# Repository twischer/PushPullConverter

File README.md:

PushPullConverter
=================

Half-bridge push-pull converter to convert 12 volt to higher voltage

There are assembled circuits available which reduces the complexity of this circuit and
might improve the efficiency.
Search for "EG7500 Inverter switching power driver board compatible KA7500 TL494" to find them.

Status
------
I am able to light up a 60W light bulb without rectifier secondary site in use.
But when using the rectifier the efficiency drops to ~50%.

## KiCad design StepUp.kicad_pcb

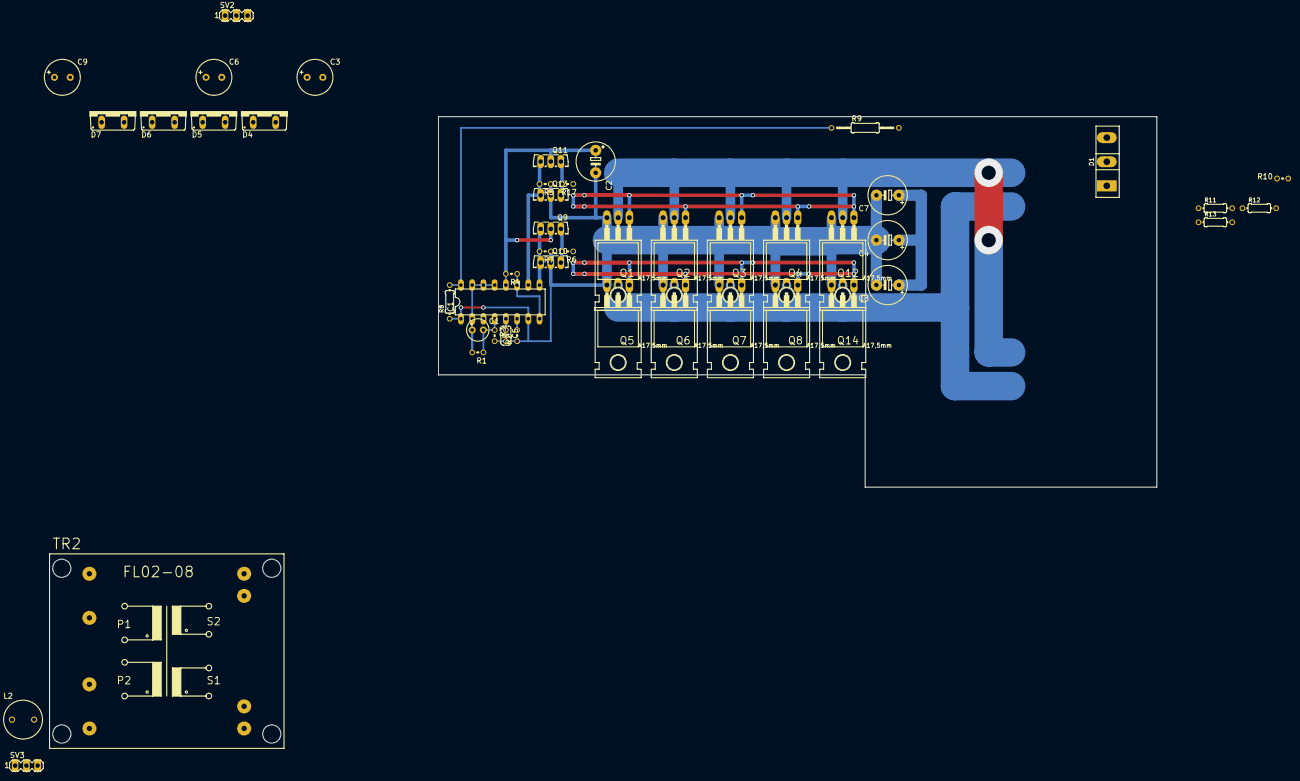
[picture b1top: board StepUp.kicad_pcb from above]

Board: 2 copper layers, 162.5 x 83.8 mm, 47 parts (0 on the bottom side), 27 nets.

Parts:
C1: 10µ; E2,5-5
C2: 1000µ; E5-8,5
C3, C6, C9: CPOL-EUE3.5-8; E3,5-8
C4, C7, C8: 3300µ; E5-8,5
C5: 1n; C025-024X044
D1: MBR20200CT; TO-247-3_Vertical
D4, D5, D6, D7: BYT08P; TO220ACS
IC1: TL494N; DIL16
L2: 10µ; 6000-XXXX-RC
Q1: IRFZ46Z; TO220BH
Q2, Q3, Q4, Q5, Q6, Q7, Q8: IRFZ46N; TO220BH
Q9, Q11: 2SD1563; TO126AV
Q10, Q13: 2SB1086; TO126AV
Q12, Q14: IRFZ48Z; TO220BH
R1: infi; 0204V
R2: 0-5k; 0204V
R3, R5, R7: 470; 0204V
R4: 22; 0204V
R6, R17: 0; 0204V
R8, R11, R12: 27k; 0204_7
R9: 330k; 0207_15
R10: 1k; 0204V
R13: 330k; 0204_7
SV2, SV3: MA03-1
TR2: FL02; FL02-08

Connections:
+12V: C2.+, IC1.12, Q9.C, Q11.C, R4.2, SV3.2
GND: C2.-, C3.-, C4.-, C5.2, C6.-, C7.-, C8.-, C9.-, D6.A, D7.A, IC1.1, IC1.7, Q1.S, Q2.S, Q3.S, Q4.S, Q5.S, Q6.S, Q7.S, Q8.S, Q10.C, Q12.S, Q13.C, Q14.S, R2.1, R3.2, R5.1, R7.1, R8.1, SV2.2, SV3.1
unnamed: C1.+, IC1.13, IC1.14, IC1.15, R1.2, R11.1
unnamed: C1.-, IC1.4, R1.1, R3.1
unnamed: C4.+, C7.+, C8.+, L2.2, TR2.2, TR2.3
unnamed: C5.1, IC1.5
unnamed: D1.1, TR2.8
unnamed: D1.3, TR2.5
unnamed: D4.A, D7.C
unnamed: D5.A, D6.C
unnamed: IC1.2, R11.2, R12.1
unnamed: IC1.6, R10.2
unnamed: IC1.9, Q9.B, Q10.B, R7.2
unnamed: IC1.10, Q11.B, Q13.B, R5.2
unnamed: IC1.8, IC1.11, R4.1
unnamed: IC1.16, R8.2, R9.1
unnamed: L2.1, SV3.3
unnamed: Q1.D, Q2.D, Q3.D, Q4.D, Q12.D, TR2.1
unnamed: Q1.G, Q2.G, Q3.G, Q4.G, Q12.G, R17.1
unnamed: Q5.D, Q6.D, Q7.D, Q8.D, TR2.4
unnamed: Q5.G, Q6.G, Q7.G, Q8.G, R6.1
unnamed: Q9.E, Q10.E, R6.2
unnamed: Q11.E, Q13.E, R17.2
unnamed: R2.2, R10.1
unnamed: R12.2, R13.1
unnamed: TR2.6, TR2.7
V+: C3.+, C6.+, C9.+, D4.C, D5.C, R9.2, SV2.1

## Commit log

2014-10-07 Use simple MOSFET driver (only usefull for small MOSFETs
2014-10-07 Use class C bridge as MOSFET driver
2021-01-15 Add license
2021-01-15 Update current status
2021-01-15 Convert to kicad
